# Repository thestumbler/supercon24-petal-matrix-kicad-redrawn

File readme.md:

# Redrawing Hackaday Supercon 2024 Petal Matrix SAO in Kicad

Making a KiCad version of the Supercon 2024 Petal Matrix SAO.

See the related [Hackaday blog article](
https://hackaday.com/2024/11/19/supercon-2024-sao-petal-kicad-redrawing-project).

* [Schematic drawing (PDF)](sao-petal-sch.pdf))
* [PCB top drawing (PDF)](sao-petal-pcb.pdf)

## Original Drawings

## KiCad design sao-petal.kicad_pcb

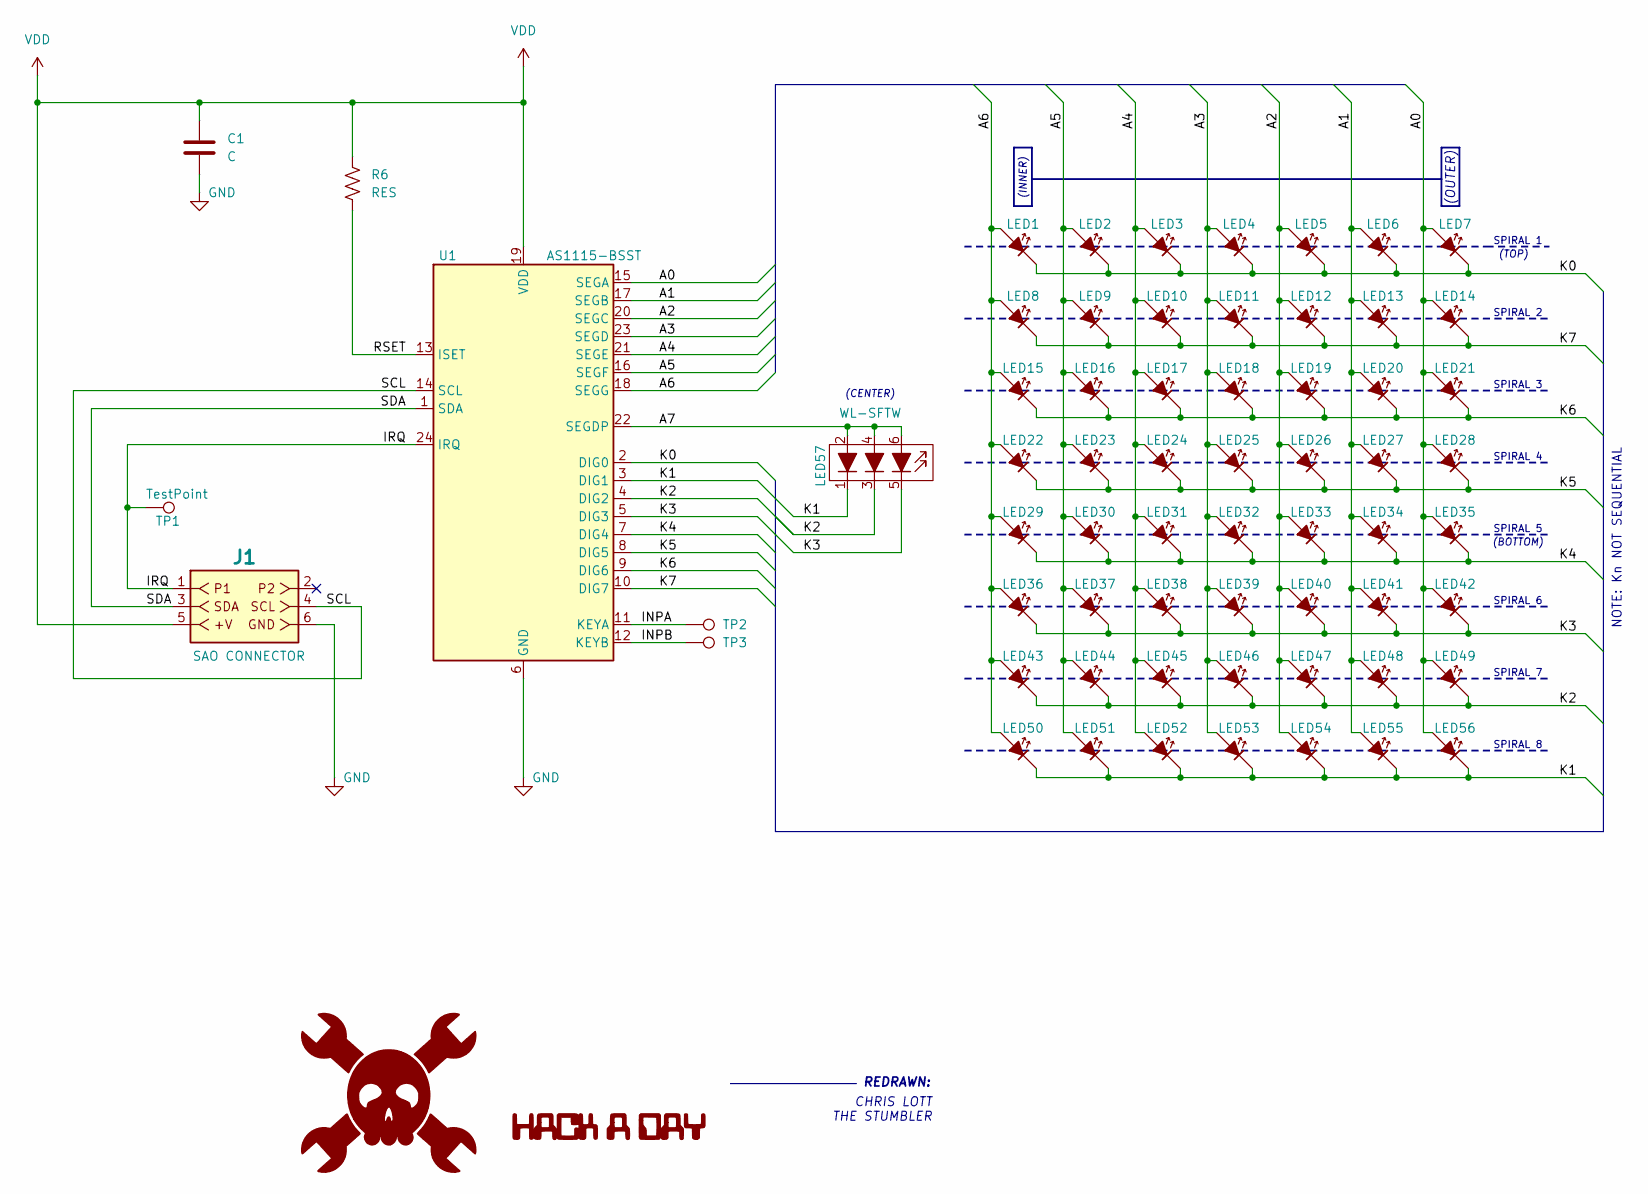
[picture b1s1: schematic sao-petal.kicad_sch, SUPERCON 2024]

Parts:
C1: C; R_0603_1608Metric_SAO
J1: SAO CONNECTOR; SAO_PIN_HEADER_2x03
LED1, LED2, LED3, LED4, LED5, LED6, LED7, LED8, LED9, LED10, LED11, LED12, LED13, LED14, LED15, LED16, LED17, LED18, LED19, LED20, LED21, LED22, LED23, LED24, LED25, LED26, LED27, LED28, LED29, LED30, LED31, LED32, LED33, LED34, LED35, LED36, LED37, LED38, LED39, LED40, LED41, LED42, LED43, LED44, LED45, LED46, LED47, LED48, LED49, LED50, LED51, LED52, LED53, LED54, LED55, LED56: LED45; LED_0603_1608Metric-SAO
LED57: WL-SFTW; LED_WS2812_PLCC6_5.0x5.0mm_P1.6mm-SAO
R6: RES; R_0603_1608Metric_SAO
TP1, TP2, TP3: TestPoint; TestPoint_Plated_Hole-SAO
U1: AS1115-BSST; QSOP-24_3.9x8.7mm_P0.635mm-SAO

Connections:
/A0: LED7.1 (A), LED14.1 (A), LED21.1 (A), LED28.1 (A), LED35.1 (A), LED42.1 (A), LED49.1 (A), LED56.1 (A), U1.15 (SEGA)
/A1: LED6.1 (A), LED13.1 (A), LED20.1 (A), LED27.1 (A), LED34.1 (A), LED41.1 (A), LED48.1 (A), LED55.1 (A), U1.17 (SEGB)
/A2: LED5.1 (A), LED12.1 (A), LED19.1 (A), LED26.1 (A), LED33.1 (A), LED40.1 (A), LED47.1 (A), LED54.1 (A), U1.20 (SEGC)
/A3: LED4.1 (A), LED11.1 (A), LED18.1 (A), LED25.1 (A), LED32.1 (A), LED39.1 (A), LED46.1 (A), LED53.1 (A), U1.23 (SEGD)
/A4: LED3.1 (A), LED10.1 (A), LED17.1 (A), LED24.1 (A), LED31.1 (A), LED38.1 (A), LED45.1 (A), LED52.1 (A), U1.21 (SEGE)
/A5: LED2.1 (A), LED9.1 (A), LED16.1 (A), LED23.1 (A), LED30.1 (A), LED37.1 (A), LED44.1 (A), LED51.1 (A), U1.16 (SEGF)
/A6: LED1.1 (A), LED8.1 (A), LED15.1 (A), LED22.1 (A), LED29.1 (A), LED36.1 (A), LED43.1 (A), LED50.1 (A), U1.18 (SEGG)
/A7: LED57.2 (A), LED57.4 (A), LED57.6 (A), U1.22 (SEGDP)
/INPA: TP2.1, U1.11 (KEYA)
/INPB: TP3.1, U1.12 (KEYB)
/IRQ: J1.1, TP1.1, U1.24 (IRQ)
/K0: LED1.2 (K), LED2.2 (K), LED3.2 (K), LED4.2 (K), LED5.2 (K), LED6.2 (K), LED7.2 (K), U1.2 (DIG0)
/K1: LED50.2 (K), LED51.2 (K), LED52.2 (K), LED53.2 (K), LED54.2 (K), LED55.2 (K), LED56.2 (K), LED57.1 (K), U1.3 (DIG1)
/K2: LED43.2 (K), LED44.2 (K), LED45.2 (K), LED46.2 (K), LED47.2 (K), LED48.2 (K), LED49.2 (K), LED57.3 (K), U1.4 (DIG2)
/K3: LED36.2 (K), LED37.2 (K), LED38.2 (K), LED39.2 (K), LED40.2 (K), LED41.2 (K), LED42.2 (K), LED57.5 (K), U1.5 (DIG3)
/K4: LED29.2 (K), LED30.2 (K), LED31.2 (K), LED32.2 (K), LED33.2 (K), LED34.2 (K), LED35.2 (K), U1.7 (DIG4)
/K5: LED22.2 (K), LED23.2 (K), LED24.2 (K), LED25.2 (K), LED26.2 (K), LED27.2 (K), LED28.2 (K), U1.8 (DIG5)
/K6: LED15.2 (K), LED16.2 (K), LED17.2 (K), LED18.2 (K), LED19.2 (K), LED20.2 (K), LED21.2 (K), U1.9 (DIG6)
/K7: LED8.2 (K), LED9.2 (K), LED10.2 (K), LED11.2 (K), LED12.2 (K), LED13.2 (K), LED14.2 (K), U1.10 (DIG7)
/RSET: R6.2, U1.13 (ISET)
/SCL: J1.4, U1.14 (SCL)
/SDA: J1.3, U1.1 (SDA)
GND: C1.2, J1.6, U1.6 (GND)
VDD: C1.1, J1.5, R6.1, U1.19 (VDD)

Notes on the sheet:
NOTE: Kn NOT SEQUENTIAL
REDRAWN:
SPIRAL 6
SPIRAL 3
(BOTTOM)
SPIRAL 5
SPIRAL 7
(INNER)
(TOP)
SPIRAL 1
(CENTER)
(OUTER)
CHRIS LOTT THE STUMBLER
SPIRAL 8
SPIRAL 2
SPIRAL 4

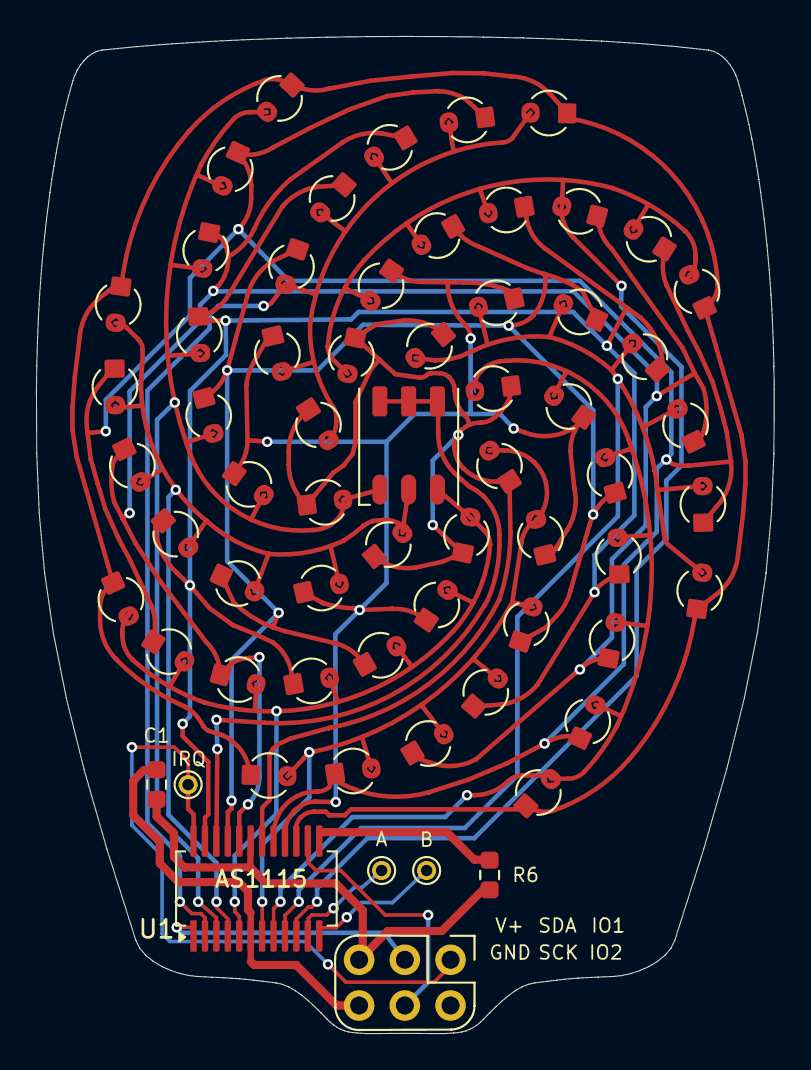
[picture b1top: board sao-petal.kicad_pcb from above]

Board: 2 copper layers, 41.0 x 55.4 mm, 64 parts (0 on the bottom side), 24 nets.

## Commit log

2024-11-15 added detail image for discrepancy at test points
2024-11-20 added link to hackaday article
2024-11-20 fixed the link
